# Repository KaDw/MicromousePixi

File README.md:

# Micromouse Pixi #
	
|  |  |
| ----- | ----- |
| Width   | 74mm  |
| Length  | 88mm  |
| Weight  |   |
| Wheels  | 3D printed wheels + MZT-302-30 tyres  |
| Microcontroller  | STM32F405RGT6  |
| Motor/Encoder  | Pololu 10:1 HPCB 3000 obr/min + AS5304 encoders  |
| Battery  | Li-Pol Dualsky 7.4V 150mAh 20C  |
| Motor Driver  | TB6612  |
| Sensor | TEFT4300 + SFH4545 X 6  |
| Gyro | FXAS21002C  |

PCB

### Development tools ###

* STM32CubeMX Version 4.17.0
* HAL Libraries - FW_F4 V1.13.1
* Keil uVision 5.21a
* EagleCAD 7.2
* Autodesk Inventor 2016

Development tools can downloaded [here](https://drive.google.com/open?id=0B6SlddUSFtelRTBFR0EwWk1qT1k)

### Setup ###

* CubeMX setup
You can get HAL libraries by going to Help->Install New Libraries->Firmware PAckage for Family STM32F4.
...

### Who do I talk to? ###

* Karol Trzciński 
* Karol Dworakowski karol1dw@gmail.com

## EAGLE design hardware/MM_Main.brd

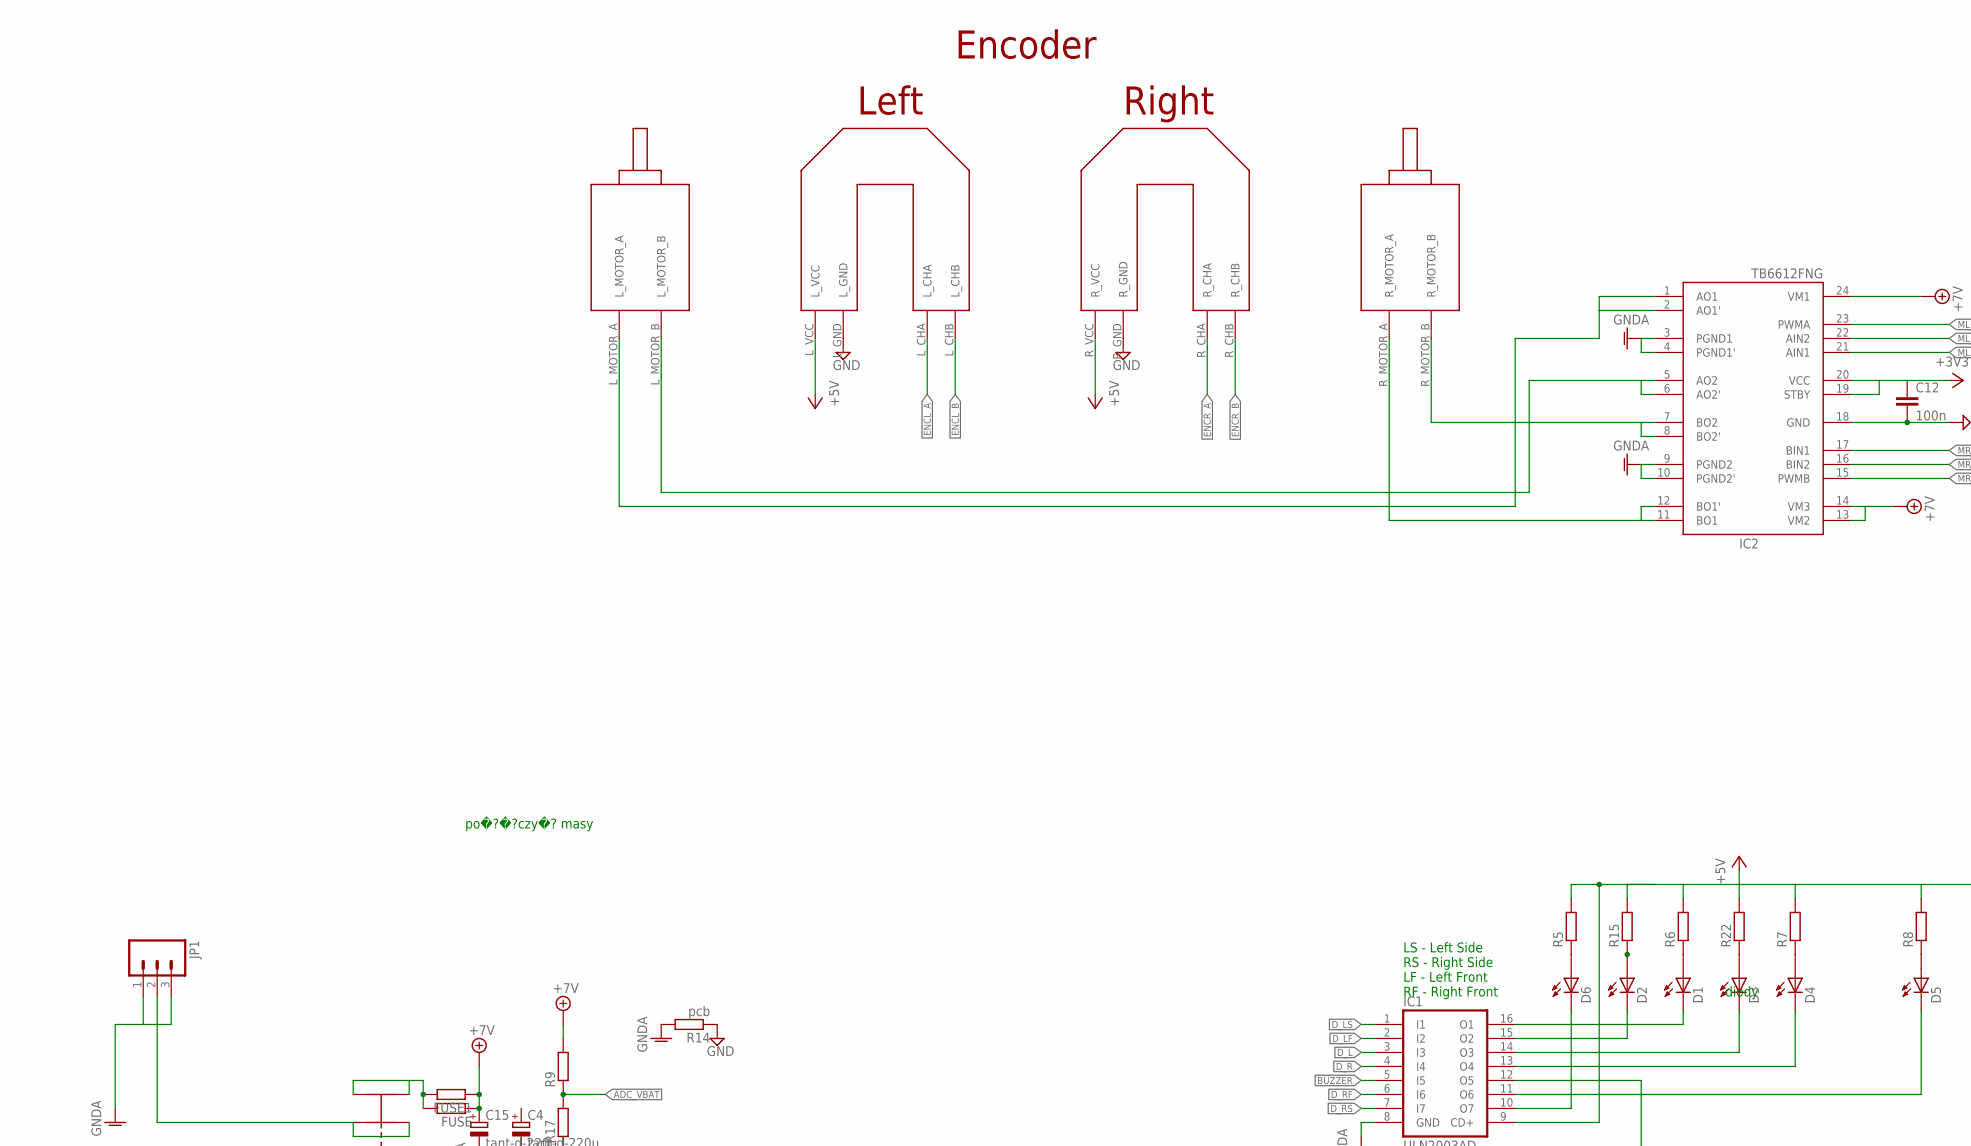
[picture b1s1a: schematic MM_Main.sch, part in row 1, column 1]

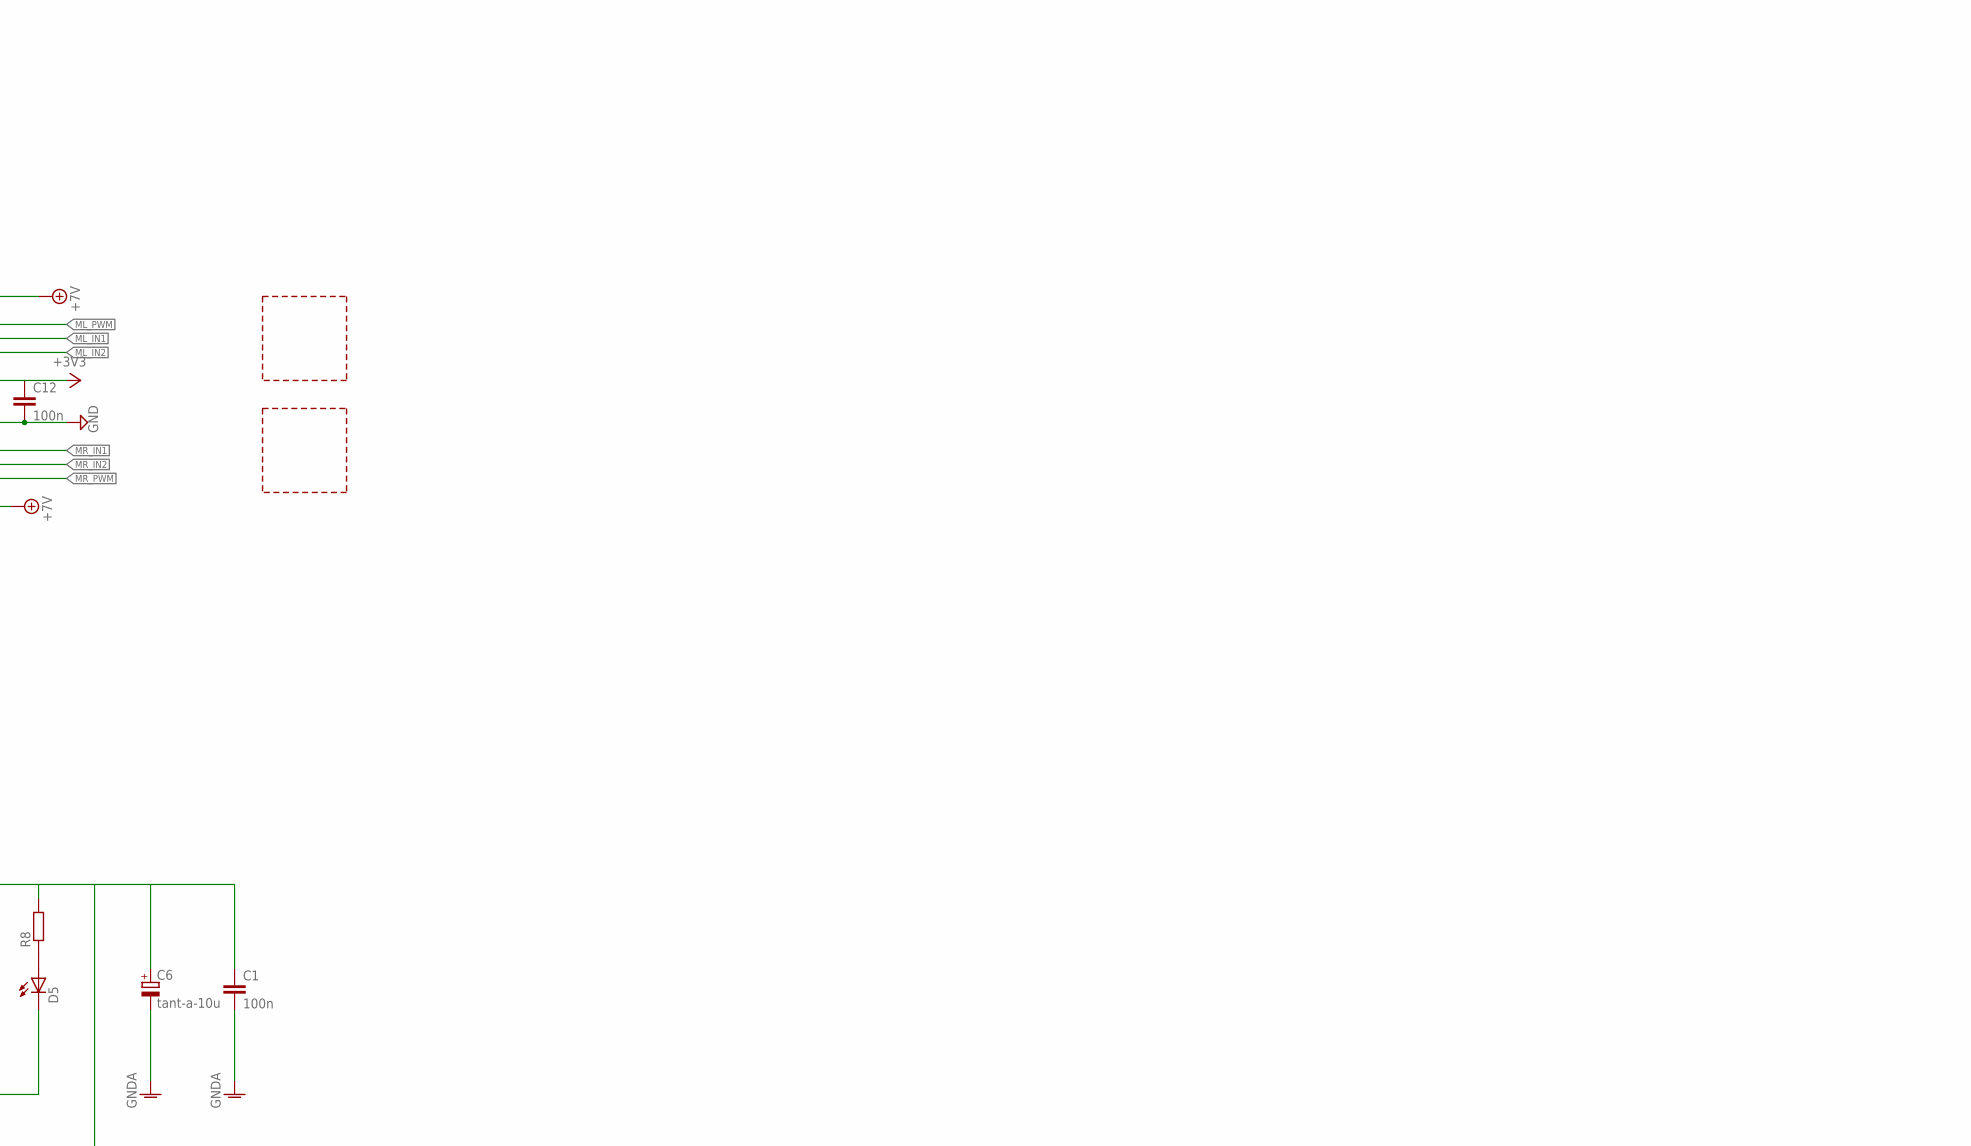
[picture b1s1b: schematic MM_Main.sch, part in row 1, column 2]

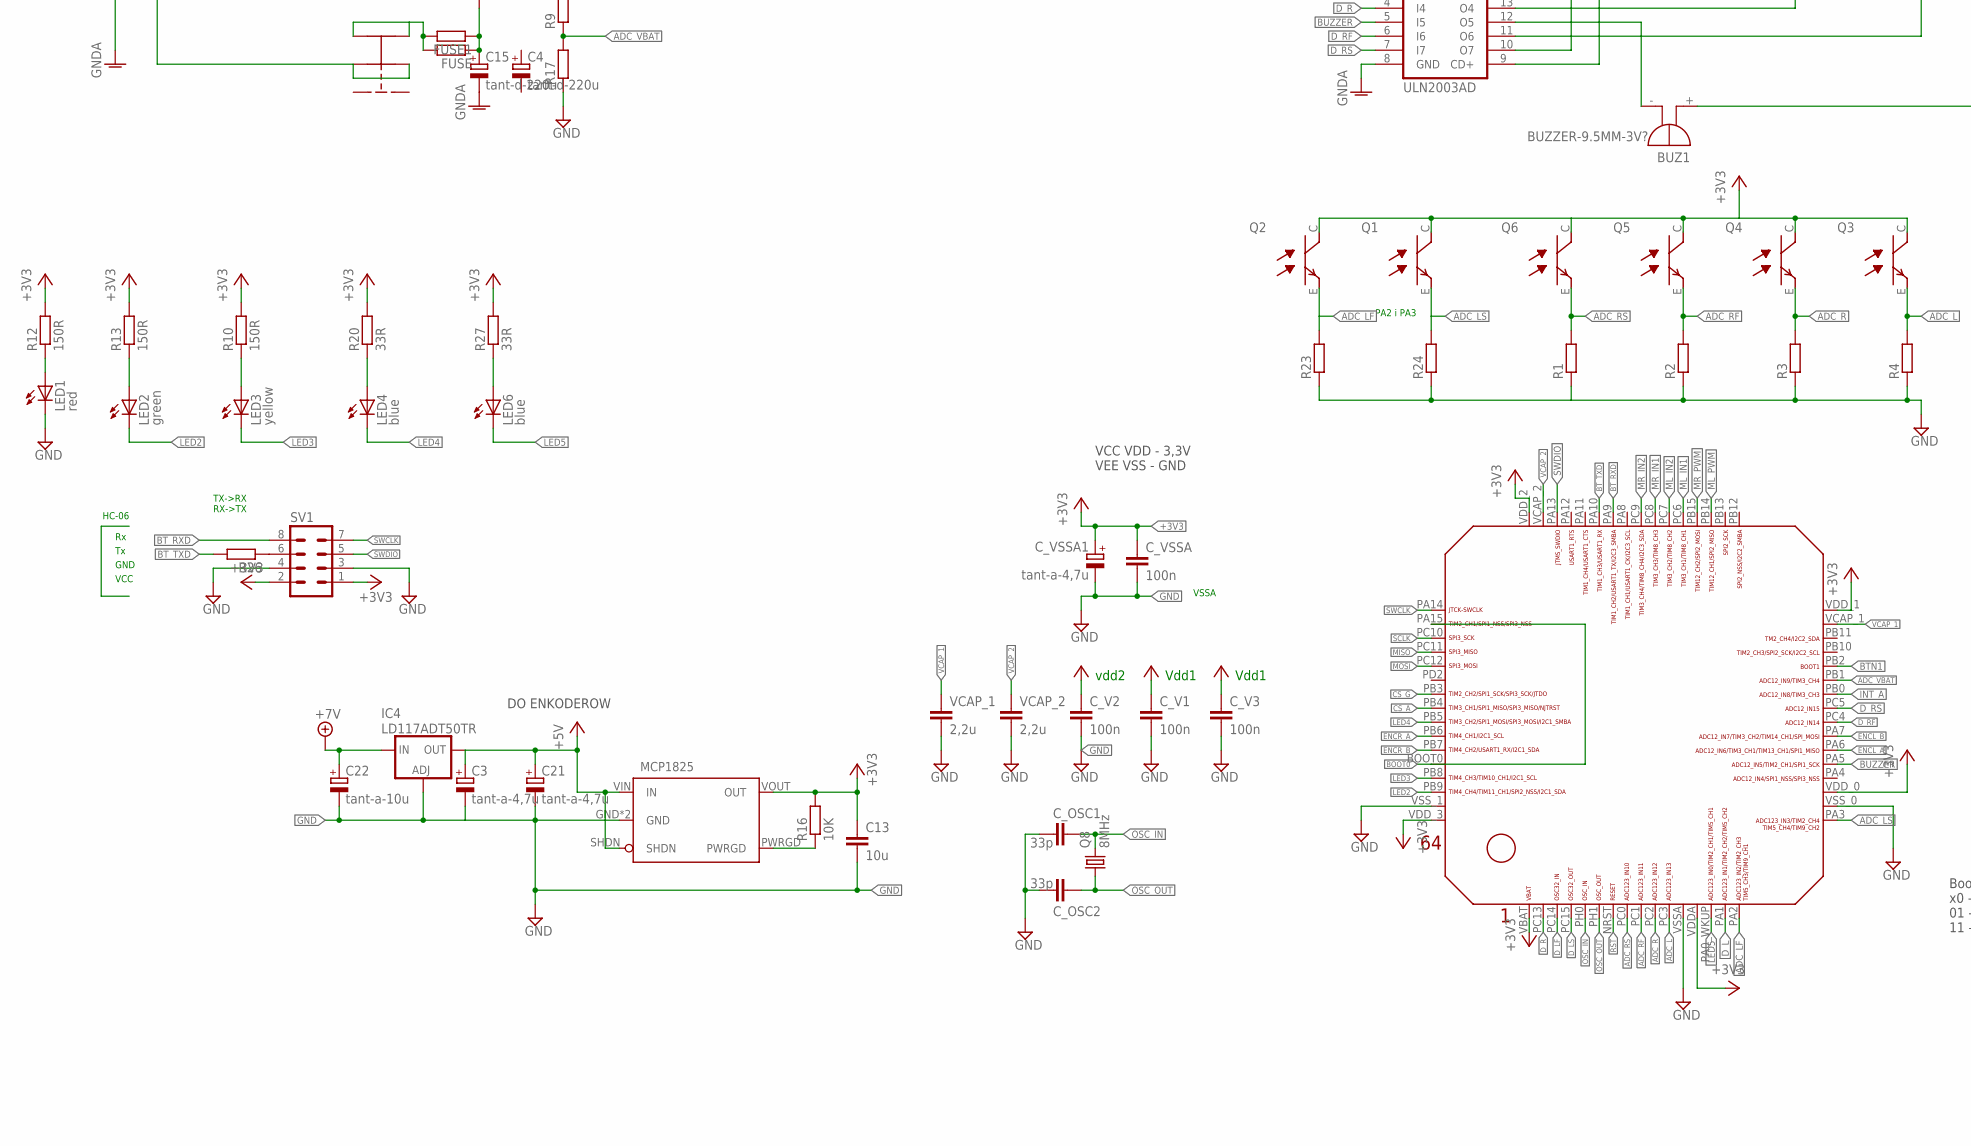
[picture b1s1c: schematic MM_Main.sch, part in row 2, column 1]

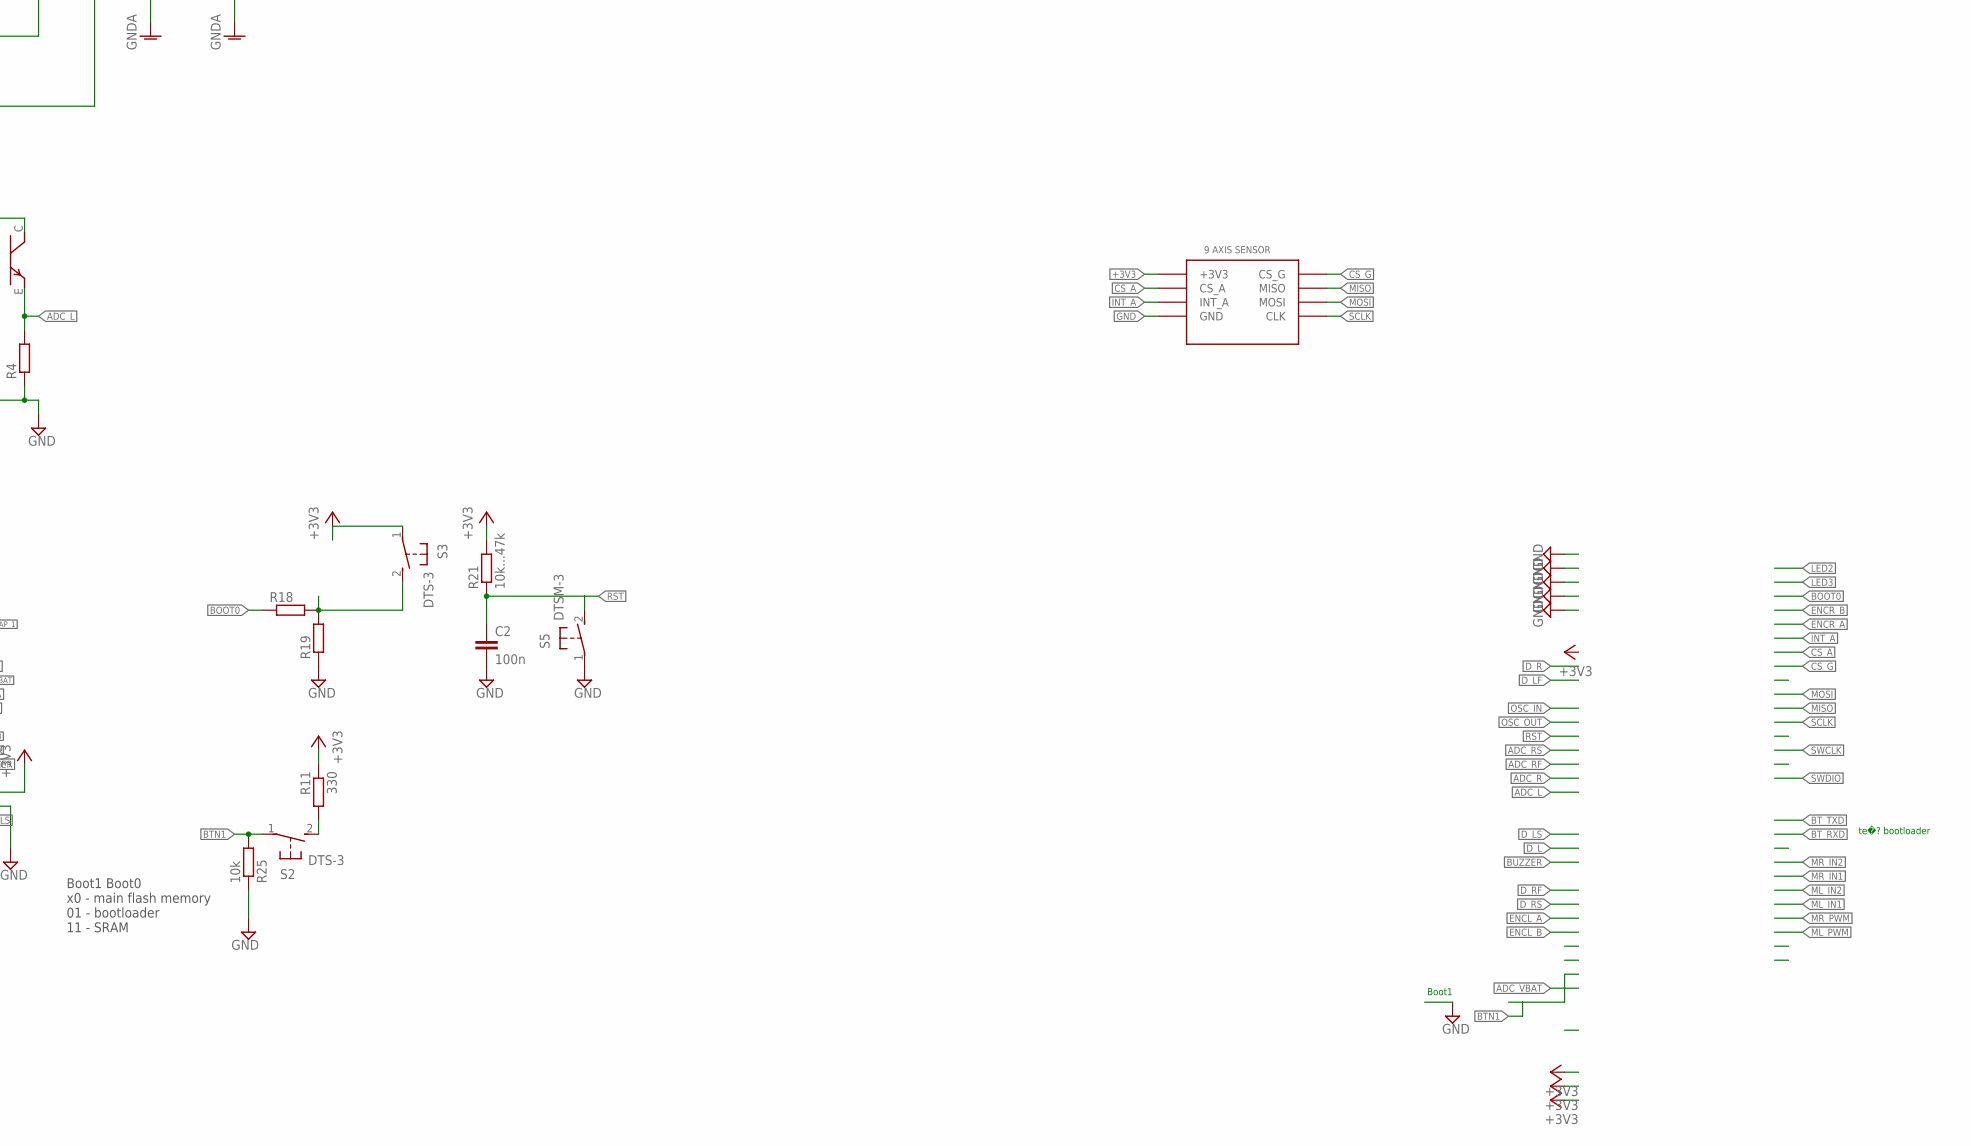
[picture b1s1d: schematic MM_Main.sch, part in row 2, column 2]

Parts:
BUZ1: BUZZER-9.5MM-3V?; BUZZER-9.5MM
C1, C2: 100n; C0805
C3, C21: tant-a-4,7u; SMC_A
C4, C15: tant-d-220u; SMC_D
C6, C22: tant-a-10u; SMC_A
C12: 100n; C0603
C13: 10u; C0805
C_OSC1, C_OSC2: 33p; C0805
C_V1, C_V2, C_V3: 100n; C0805
C_VSSA: 100n; C0805
C_VSSA1: tant-a-4,7u; SMC_A
D1, D2, D3, D4, D5, D6: SFH4545-C
FUSE, FUSE1: R-EU_M3516; M3516
IC1: ULN2003AD; SO16
IC2: TB6612FNG; SSOP24
IC4: LD117ADT50TR; DPACK
IC5: MCP1825; SOT223-5
JP1: M03POLAR; MOLEX-1X3
L1, L2: LABITYNT; LABIRYNT
LED1: red; SML1206
LED2: green; SML1206
LED3: yellow; SML1206
LED4, LED6: blue; SML1206
Q1, Q2, Q3, Q4, Q5, Q6: TEFT4300
Q8: 8MHz; CRYSTAL_5X3.2MM
R1, R2, R3, R4, R5, R6, R7, R8, R9, R15, R17, R18, R19, R22, R23, R24, R26: R-EU_R0805; R0805
R10, R12, R13: 150R; R0805
R11: 330; R0805
R14: pcb; R0201
R16: 10K; R0805
R20, R27: 33R; R0805
R21: 10k...47k; R0805
R25: 10k; R0805
S2, S3: DTS-3
S5: DTSM-3
SV1: MA04-2
U$1: 9AXIS_MODULE; 9AXIS_SENSOR_MODULE
U$3: PRZELACZNIK_SUWAKOWY
U$5: MOTOR_MOUNT
U$6: STM32F4X5; STM32F4-LQFP64
VCAP_1, VCAP_2: 2,2u; C0805

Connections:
+3V3: C12.1, C13.1, C_V1.1, C_V2.1, C_V3.1, C_VSSA.1, C_VSSA1.+, IC2.19 (STBY), IC2.20 (VCC), IC5.VOUT (OUT), Q1.C, Q2.C, Q3.C, Q4.C, Q5.C, Q6.C, R10.2, R11.1, R12.2, R13.2, R16.2, R20.2, R21.2, R27.2, S3.1, SV1.1, SV1.2, U$1.P$1 (+3V3), U$6.VBAT, U$6.VDDA, U$6.VDD_0, U$6.VDD_1, U$6.VDD_2, U$6.VDD_3
+5V: BUZ1.+, C1.1, C3.+, C6.+, C21.+, IC1.9 (CD+), IC4.4 (OUT), IC5.SHDN, IC5.VIN (IN), R5.2, R6.2, R7.2, R8.2, R15.2, R22.2, U$5.L_VCC, U$5.R_VCC
+7V: C15.+, C22.+, FUSE.1, FUSE1.1, IC2.13 (VM2), IC2.14 (VM3), IC2.24 (VM1), IC4.3 (IN), R9.2
ADC_L: Q3.E, R4.2, U$6.PC3
ADC_LF: Q2.E, R23.2, U$6.PA2
ADC_LS: Q1.E, R24.2, U$6.PA3
ADC_R: Q4.E, R3.2, U$6.PC2
ADC_RF: Q5.E, R2.2, U$6.PC1
ADC_RS: Q6.E, R1.2, U$6.PC0
ADC_VBAT: R9.1, R17.2, U$6.PB1
BOOT0: R18.1, U$6.BOOT0, U$6.PA15
BTN1: R25.2, S2.1, U$6.PB2
BT_RXD: SV1.8, U$6.PA9
BT_TXD: R26.2, U$6.PA10
BUZZER: IC1.5 (I5), U$6.PA5
CS_A: U$1.P$2 (CS_A), U$6.PB4
CS_G: U$1.P$8 (CS_G), U$6.PB3
D_L: IC1.3 (I3), U$6.PA1
D_LF: IC1.2 (I2), U$6.PC14
D_LS: IC1.1 (I1), U$6.PC15
D_R: IC1.4 (I4), U$6.PC13
D_RF: IC1.6 (I6), U$6.PC4
D_RS: IC1.7 (I7), U$6.PC5
ENCL_A: U$5.L_CHA, U$6.PA6
ENCL_B: U$5.L_CHB, U$6.PA7
ENCR_A: U$5.R_CHA, U$6.PB6
ENCR_B: U$5.R_CHB, U$6.PB7
GND: C2.2, C3.-, C12.2, C13.2, C21.-, C22.-, C_OSC1.1, C_OSC2.1, C_V1.2, C_V2.2, C_V3.2, C_VSSA.2, C_VSSA1.-, IC2.18 (GND), IC4.1 (ADJ), IC5.GND, IC5.GND_TAB (GND), LED1.C, R1.1, R2.1, R3.1, R4.1, R14.1, R17.1, R19.1, R23.1, R24.1, R25.1, S5.1, SV1.3, SV1.4, U$1.P$4 (GND), U$5.L_GND, U$5.R_GND, U$6.VSSA, U$6.VSS_0, U$6.VSS_1, VCAP_1.2, VCAP_2.2
GNDA: C1.2, C6.-, C15.-, IC1.8 (GND), IC2.3 (PGND1), IC2.4 (PGND1'), IC2.9 (PGND2), IC2.10 (PGND2'), JP1.1, JP1.3, R14.2
INT_A: U$1.P$3 (INT_A), U$6.PB0
LED2: LED2.C, U$6.PB9
LED3: LED3.C, U$6.PB8
LED4: LED4.C, U$6.PB5
LED5: LED6.C, U$6.PA0_WKUP (PA0_AKUP)
MISO: U$1.P$7 (MISO), U$6.PC11
ML_IN1: IC2.22 (AIN2), U$6.PC6
ML_IN2: IC2.21 (AIN1), U$6.PC7
ML_PWM: IC2.23 (PWMA), U$6.PB14
MOSI: U$1.P$6 (MOSI), U$6.PC12
MR_IN1: IC2.17 (BIN1), U$6.PC8
MR_IN2: IC2.16 (BIN2), U$6.PC9
MR_PWM: IC2.15 (PWMB), U$6.PB15
unnamed: IC5.PWRGD, R16.1
unnamed: D2.ANODA (A), R15.1
unnamed: D6.ANODA (A), R5.1
unnamed: IC2.7 (BO2), IC2.8 (BO2'), U$5.R_MOTOR_B
unnamed: IC2.11 (BO1), IC2.12 (BO1'), U$5.R_MOTOR_A
unnamed: IC2.1 (AO1), IC2.2 (AO1'), U$5.L_MOTOR_A
unnamed: LED3.A, R10.1
unnamed: D1.ANODA (A), R6.1
unnamed: D4.ANODA (A), R7.1
unnamed: D5.ANODA (A), R8.1
unnamed: LED1.A, R12.1
unnamed: IC2.5 (AO2), IC2.6 (AO2'), U$5.L_MOTOR_B
unnamed: BUZ1.-, IC1.12 (O5)
unnamed: D3.ANODA (A), R22.1
unnamed: LED2.A, R13.1
unnamed: LED4.A, R20.1
unnamed: R18.2, R19.2, S3.2
unnamed: FUSE.2, FUSE1.2, U$3.3, U$3.6
unnamed: R26.1, SV1.6
unnamed: R11.2, S2.2
unnamed: LED6.A, R27.1
unnamed: JP1.2, U$3.2, U$3.5
OSC_IN: C_OSC1.2, Q8.P$2 (2), U$6.PH0
OSC_OUT: C_OSC2.2, Q8.P$1 (1), U$6.PH1
RST: C2.1, R21.1, S5.2, U$6.NRST
SCLK: U$1.P$5 (CLK), U$6.PC10
SENSOR_L: D3.KATODA (C), IC1.14 (O3)
SENSOR_LF: D2.KATODA (C), IC1.15 (O2)
SENSOR_LS: D1.KATODA (C), IC1.16 (O1)
SENSOR_R: D4.KATODA (C), IC1.13 (O4)
SENSOR_RF: D5.KATODA (C), IC1.11 (O6)
SENSOR_RS: D6.KATODA (C), IC1.10 (O7)
SWCLK: SV1.7, U$6.PA14
SWDIO: SV1.5, U$6.PA13
VCAP_1: U$6.VCAP_1, VCAP_1.1
VCAP_2: U$6.VCAP_2, VCAP_2.1

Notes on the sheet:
diody
Boot1 Boot0 x0 - main flash memory 01 - bootloader 11 - SRAM
DO ENKODEROW
te�? bootloader
Boot1
VSSA
po�?�?czy�? masy
Vdd1
vdd2
VCC VDD - 3,3V VEE VSS - GND
TX->RX RX->TX
PA2 i PA3
GND
VCC
HC-06
LS - Left Side RS - Right Side LF - Left Front RF - Right Front

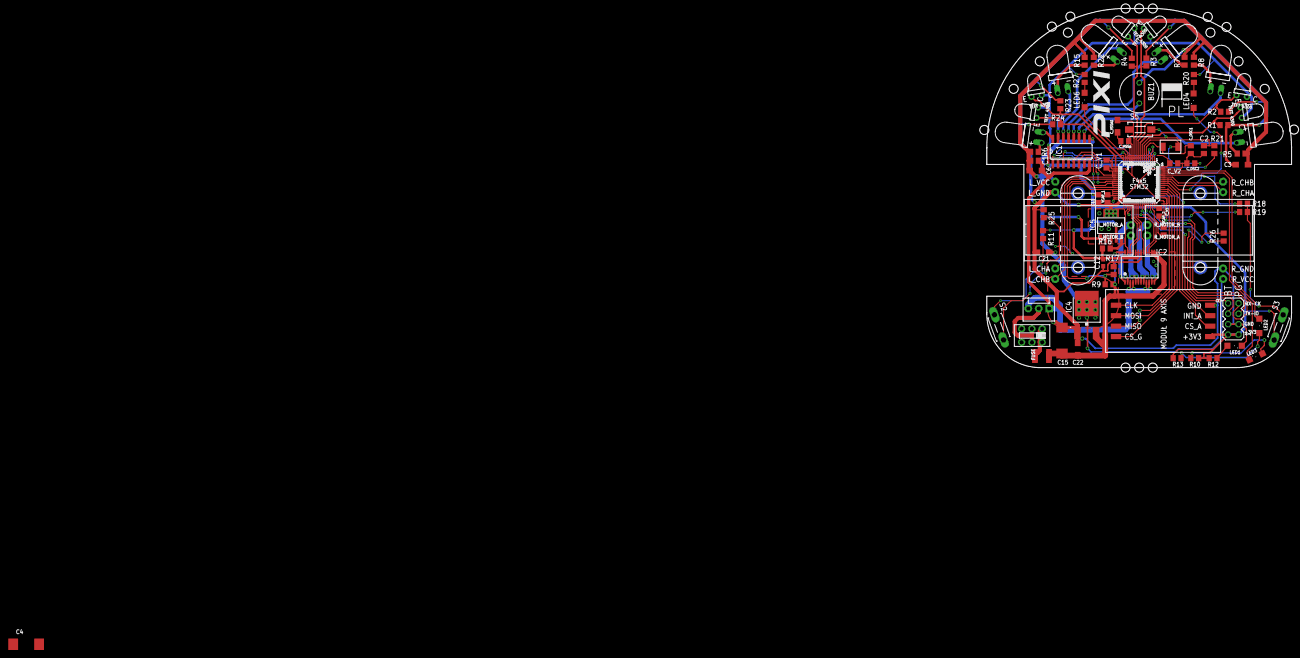
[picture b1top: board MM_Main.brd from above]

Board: 2 copper layers, 74.0 x 87.2 mm, 82 parts (0 on the bottom side), 78 nets.

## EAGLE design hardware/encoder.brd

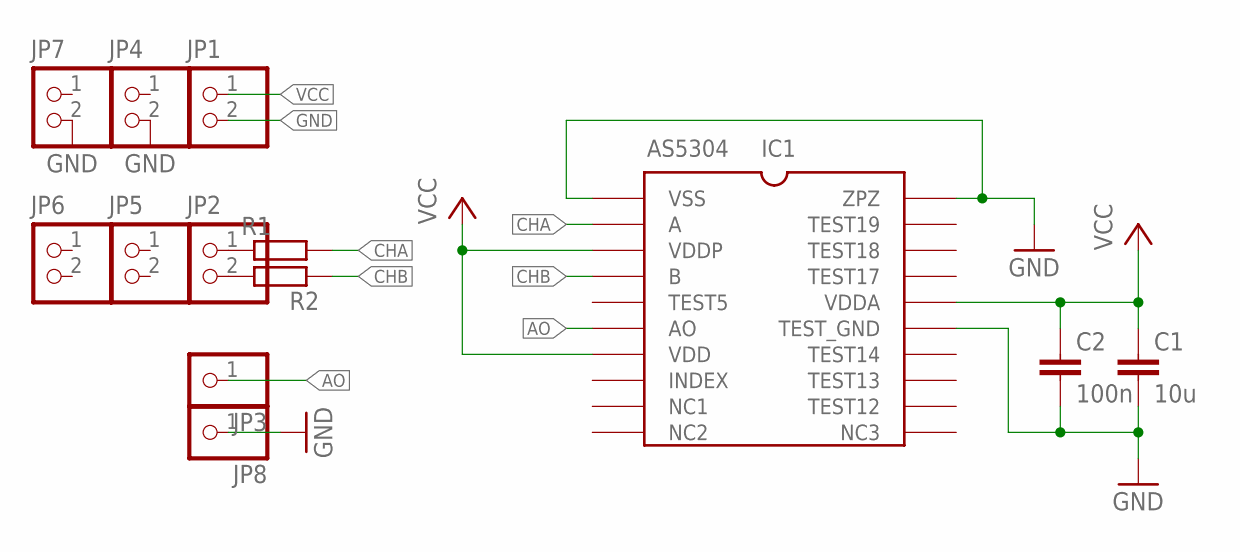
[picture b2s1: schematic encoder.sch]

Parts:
C1: 10u; C0603
C2: 100n; C0603
IC1: AS5304; TSSOP20
JP1, JP2, JP4, JP5, JP6, JP7: PINHD_1X2_ROUND
JP3, JP8: PINHD-1X1; 1X01
R1, R2: R-EU_R0805; R0805

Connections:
AO: IC1.AO, JP3.1
CHA: IC1.A, R1.2
CHB: IC1.B, R2.1
GND: C1.2, C2.2, IC1.TEST_GND, IC1.VSS, IC1.ZPZ, JP1.2, JP4.2, JP7.2, JP8.1
unnamed: JP2.1, R1.1
unnamed: JP2.2, R2.2
VCC: C1.1, C2.1, IC1.VDD, IC1.VDDA, IC1.VDDP, JP1.1

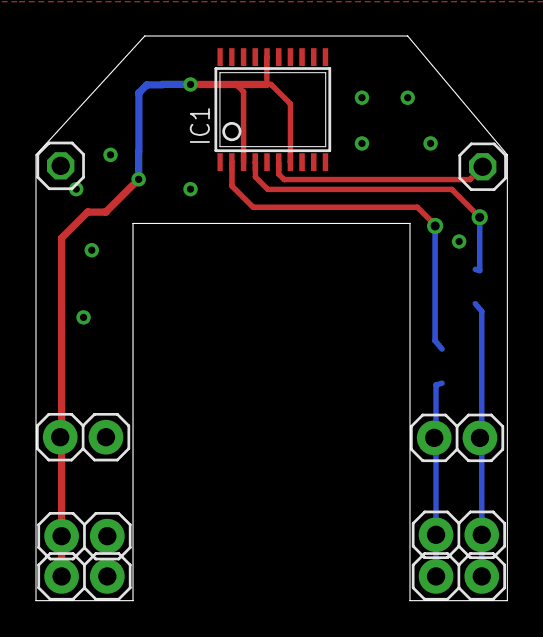
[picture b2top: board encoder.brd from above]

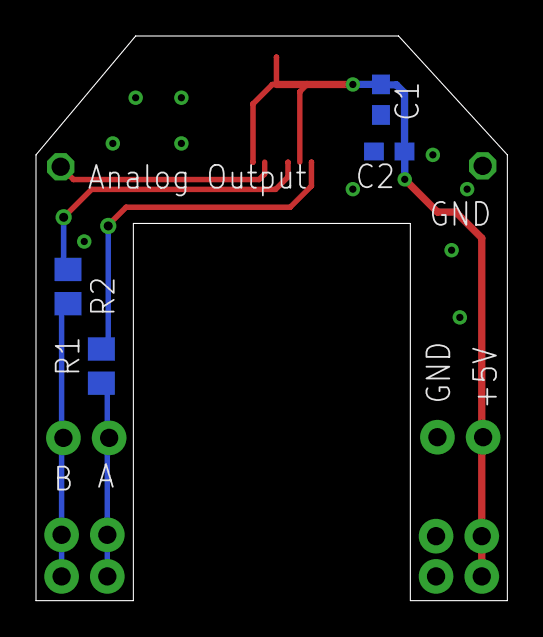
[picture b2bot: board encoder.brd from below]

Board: 2 copper layers, 26.2 x 31.4 mm, 13 parts (4 on the bottom side), 7 nets.

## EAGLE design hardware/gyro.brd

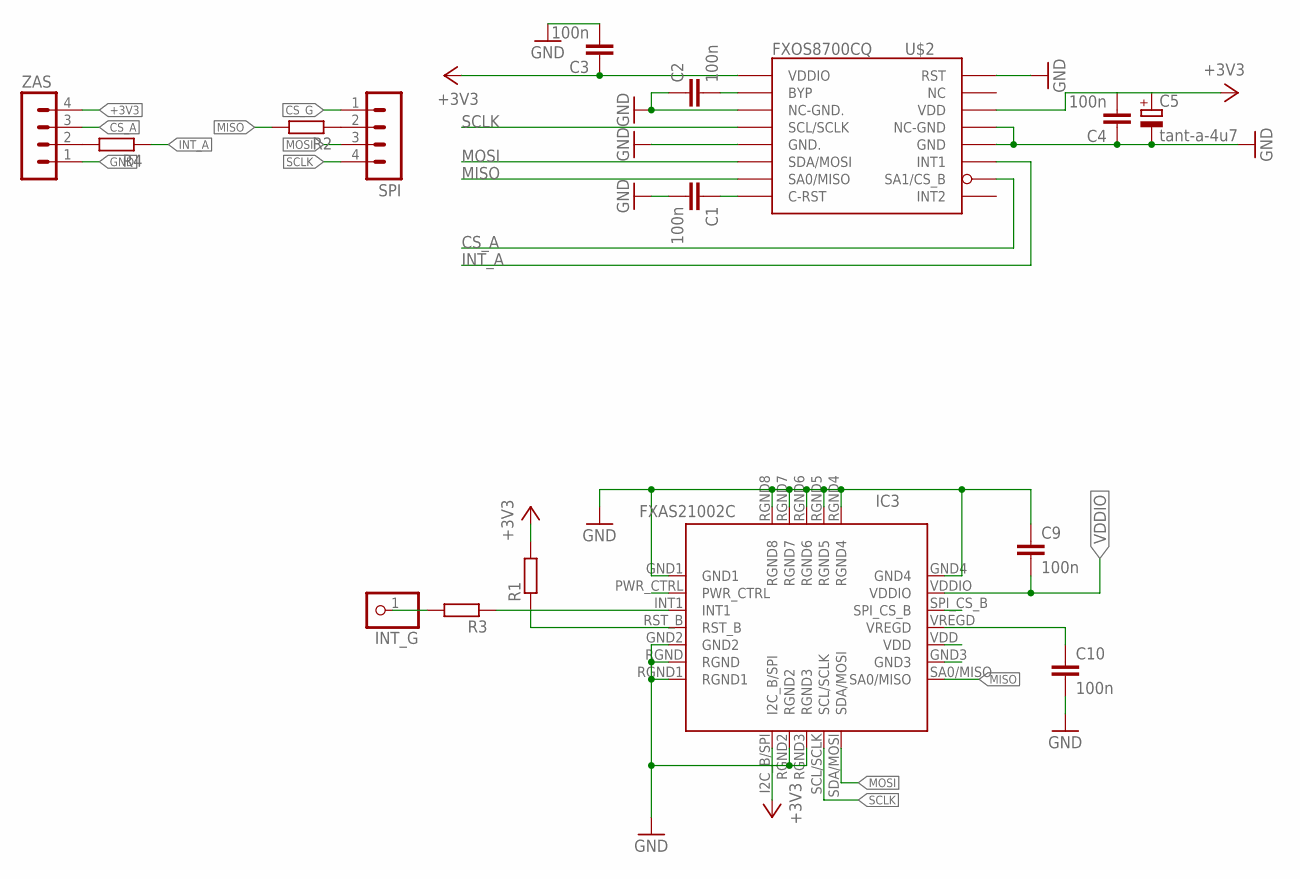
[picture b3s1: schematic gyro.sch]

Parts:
C1, C2, C3, C4, C9, C10: 100n; C0603
C5: tant-a-4u7; SMC_A
IC3: FXAS21002C; QFN24-4X4
INT_G: PINHD-1X1; 1X01
R1, R2, R3, R4: R-EU_R0603; R0603
SPI: MA04-1
U$2: FXOS8700CQR1; QFN16-5X3
ZAS: MA04-1

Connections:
+3V3: C3.1, C4.2, C5.+, IC3.I2C_B/SPI, IC3.VDD, R1.2, U$2.P$1 (VDDIO), U$2.P$14 (VDD), ZAS.4
CS_A: U$2.P$10 (SA1/CS_B), ZAS.3
CS_G: IC3.SPI_CS_B, SPI.1
GND: C1.2, C2.1, C3.2, C4.1, C5.-, C9.1, C10.2, IC3.GND1, IC3.GND2, IC3.GND3, IC3.GND4, IC3.RGND, IC3.RGND1, IC3.RGND2, IC3.RGND3, IC3.RGND4, IC3.RGND5, IC3.RGND6, IC3.RGND7, IC3.RGND8, U$2.P$3 (NC-GND.), U$2.P$5 (GND.), U$2.P$12 (GND), U$2.P$13 (NC-GND), U$2.P$16 (RST), ZAS.1
INT_A: R4.1, U$2.P$11 (INT1)
MISO: IC3.SA0/MISO, R2.2, U$2.P$7 (SA0/MISO)
MOSI: IC3.SDA/MOSI, SPI.3, U$2.P$6 (SDA/MOSI)
unnamed: R2.1, SPI.2
unnamed: INT_G.1, R3.2
unnamed: IC3.INT1, R3.1
unnamed: R4.2, ZAS.2
unnamed: C1.1, U$2.P$8 (C-RST)
unnamed: C2.2, U$2.P$2 (BYP)
unnamed: C10.1, IC3.VREGD
unnamed: IC3.RST_B, R1.1
SCLK: IC3.SCL/SCLK, SPI.4, U$2.P$4 (SCL/SCLK)
VDDIO: C9.2, IC3.VDDIO

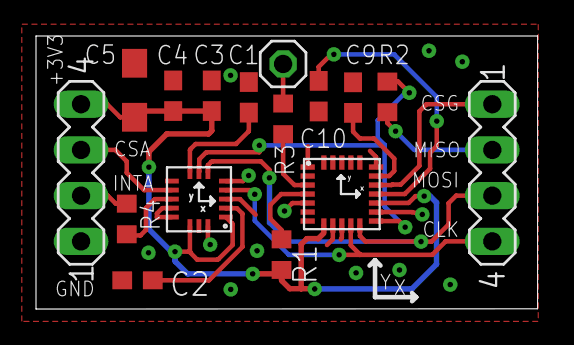
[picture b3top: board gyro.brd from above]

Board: 2 copper layers, 27.9 x 15.2 mm, 16 parts (0 on the bottom side), 17 nets.

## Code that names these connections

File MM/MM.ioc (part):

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Mcu.Name=STM32F405RGTx
Mcu.Package=LQFP64
Mcu.UserName=STM32F405RGTx
PA0-WKUP.GPIOParameters=GPIO_Label
PA0-WKUP.GPIO_Label=LED5
PA0-WKUP.Signal=GPIO_Output
PA1.GPIOParameters=GPIO_Label
PA1.GPIO_Label=D_L
PA1.Signal=GPIO_Output
PA10.GPIOParameters=GPIO_Label
PA10.GPIO_Label=BT_TX
PA10.Mode=Asynchronous
PA10.Signal=USART1_RX
PA13.Mode=Serial-Wire
PA13.Signal=SYS_JTMS-SWDIO
PA14.Mode=Serial-Wire
PA14.Signal=SYS_JTCK-SWCLK
PA15.GPIOParameters=GPIO_Label
PA15.GPIO_Label=BTN0
PA15.Signal=GPXTI15
PA2.GPIOParameters=GPIO_Label
PA2.GPIO_Label=ADC_LF
PA2.Signal=ADCx_IN2
PA3.GPIOParameters=GPIO_Label
PA3.GPIO_Label=ADC_LS
PA3.Signal=ADCx_IN3
PA5.GPIOParameters=GPIO_Label
PA5.GPIO_Label=BUZZER
PA5.Signal=GPIO_Output
PA6.GPIOParameters=GPIO_Label
PA6.GPIO_Label=ENCL_A
PA6.Signal=S_TIM3_CH1
PA7.GPIOParameters=GPIO_Label
PA7.GPIO_Label=ENCL_B
PA7.Signal=S_TIM3_CH2
PA9.GPIOParameters=GPIO_Label
PA9.GPIO_Label=BT_TX
PA9.Mode=Asynchronous
PA9.Signal=USART1_TX
PB0.GPIOParameters=GPIO_Label
PB0.GPIO_Label=INT_A
PB0.Signal=GPIO_Input
PB1.GPIOParameters=GPIO_Label
PB1.GPIO_Label=ADC1_VBAT
PB1.Signal=ADCx_IN9
PB14.GPIOParameters=GPIO_Label
PB14.GPIO_Label=ML_PWM
PB14.Signal=S_TIM12_CH1
PB15.GPIOParameters=GPIO_Label
PB15.GPIO_Label=MR_PWM
PB15.Signal=S_TIM12_CH2
PB2.GPIOParameters=GPIO_Label
PB2.GPIO_Label=BTN1
PB2.Signal=GPXTI2
PB3.GPIOParameters=GPIO_Label
PB3.GPIO_Label=CS_G
PB3.Signal=GPIO_Output
PB4.GPIOParameters=GPIO_Label
PB4.GPIO_Label=CS_A
PB4.Signal=GPIO_Output
PB5.GPIOParameters=GPIO_Label
PB5.GPIO_Label=LED3
PB5.Signal=GPIO_Output
PB6.GPIOParameters=GPIO_Label
PB6.GPIO_Label=ENCR_A
PB6.Signal=S_TIM4_CH1
PB7.GPIOParameters=GPIO_Label
PB7.GPIO_Label=ENCR_B
PB7.Signal=S_TIM4_CH2
PB8.GPIOParameters=GPIO_Label
PB8.GPIO_Label=LED2
PB8.Signal=GPIO_Output
PB9.GPIOParameters=GPIO_Label
PB9.GPIO_Label=LED1
PB9.Signal=GPIO_Output
PC0.GPIOParameters=GPIO_Label
PC0.GPIO_Label=ADC_RS
PC0.Signal=ADCx_IN10
PC1.GPIOParameters=GPIO_Label
PC1.GPIO_Label=ADC_RF
PC1.Signal=ADCx_IN11
PC10.Mode=Full_Duplex_Master
PC10.Signal=SPI3_SCK
PC11.Mode=Full_Duplex_Master
PC11.Signal=SPI3_MISO
PC12.Mode=Full_Duplex_Master
PC12.Signal=SPI3_MOSI
PC13-ANTI_TAMP.GPIOParameters=GPIO_Label
PC13-ANTI_TAMP.GPIO_Label=D_R
PC13-ANTI_TAMP.Signal=GPIO_Output
PC14-OSC32_IN.GPIOParameters=GPIO_Label
PC14-OSC32_IN.GPIO_Label=D_LF
PC14-OSC32_IN.Signal=GPIO_Output
PC15-OSC32_OUT.GPIOParameters=GPIO_Label
PC15-OSC32_OUT.GPIO_Label=D_LS
PC15-OSC32_OUT.Signal=GPIO_Output
PC2.GPIOParameters=GPIO_Label
PC2.GPIO_Label=ADC_R
PC2.Signal=ADCx_IN12
PC3.GPIOParameters=GPIO_Label
PC3.GPIO_Label=ADC_L
PC3.Signal=ADCx_IN13
PC4.GPIOParameters=GPIO_Label
PC4.GPIO_Label=D_RF
PC4.Signal=GPIO_Output
PC5.GPIOParameters=GPIO_Label
PC5.GPIO_Label=D_RS
PC5.Signal=GPIO_Output
PC6.GPIOParameters=GPIO_Label
PC6.GPIO_Label=ML_IN1
PC6.Signal=GPIO_Analog
PC7.GPIOParameters=GPIO_Label
PC7.GPIO_Label=ML_IN2
PC7.Signal=GPIO_Analog
PC8.GPIOParameters=GPIO_Label
PC8.GPIO_Label=MR_IN1
PC8.Signal=GPIO_Output
PC9.GPIOParameters=GPIO_Label
PC9.GPIO_Label=MR_IN2
PC9.Signal=GPIO_Output
PH0-OSC_IN.Mode=HSE-External-Oscillator
PH0-OSC_IN.Signal=RCC_OSC_IN
PH1-OSC_OUT.Mode=HSE-External-Oscillator
PH1-OSC_OUT.Signal=RCC_OSC_OUT
RCC.HSE_VALUE=8000000
RCC.SYSCLKFreq_VALUE=168000000
RCC.SYSCLKSource=RCC_SYSCLKSOURCE_PLLCLK
board=MM

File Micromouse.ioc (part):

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Mcu.Name=STM32F405RGTx
Mcu.Package=LQFP64
Mcu.UserName=STM32F405RGTx
PA0-WKUP.GPIOParameters=GPIO_Label
PA0-WKUP.GPIO_Label=LED4
PA0-WKUP.Signal=GPIO_Output
PA1.GPIOParameters=GPIO_Label
PA1.GPIO_Label=D_L
PA1.Signal=GPIO_Output
PA10.GPIOParameters=GPIO_Label
PA10.GPIO_Label=BT_TX
PA10.Mode=Asynchronous
PA10.Signal=USART1_RX
PA13.Mode=Serial-Wire
PA13.Signal=SYS_JTMS-SWDIO
PA14.Mode=Serial-Wire
PA14.Signal=SYS_JTCK-SWCLK
PA15.GPIOParameters=GPIO_PuPd,GPIO_Label
PA15.GPIO_Label=BTN2
PA15.GPIO_PuPd=GPIO_PULLDOWN
PA15.Signal=GPXTI15
PA2.GPIOParameters=GPIO_Label
PA2.GPIO_Label=ADC_LF
PA2.Signal=ADCx_IN2
PA3.GPIOParameters=GPIO_Label
PA3.GPIO_Label=ADC_LS
PA3.Signal=ADCx_IN3
PA5.GPIOParameters=GPIO_Label
PA5.GPIO_Label=BUZZER
PA5.Signal=GPIO_Output
PA6.GPIOParameters=GPIO_PuPd,GPIO_Label
PA6.GPIO_Label=ENCL_A
PA6.GPIO_PuPd=GPIO_PULLDOWN
PA6.Signal=S_TIM3_CH1
PA7.GPIOParameters=GPIO_PuPd,GPIO_Label
PA7.GPIO_Label=ENCL_B
PA7.GPIO_PuPd=GPIO_PULLDOWN
PA7.Signal=S_TIM3_CH2
PA9.GPIOParameters=GPIO_Label
PA9.GPIO_Label=BT_TX
PA9.Mode=Asynchronous
PA9.Signal=USART1_TX
PB0.GPIOParameters=GPIO_Label,GPIO_ModeDefaultEXTI
PB0.GPIO_Label=INT_G
PB0.GPIO_ModeDefaultEXTI=GPIO_MODE_IT_FALLING
PB0.Signal=GPXTI0
PB1.GPIOParameters=GPIO_Label
PB1.GPIO_Label=ADC_VBAT
PB1.Signal=ADCx_IN9
PB14.GPIOParameters=GPIO_Label
PB14.GPIO_Label=ML_PWM
PB14.Signal=S_TIM12_CH1
PB15.GPIOParameters=GPIO_Label
PB15.GPIO_Label=MR_PWM
PB15.Signal=S_TIM12_CH2
PB2.GPIOParameters=GPIO_PuPd,GPIO_Label,GPIO_ModeDefaultEXTI
PB2.GPIO_Label=BTN
PB2.GPIO_ModeDefaultEXTI=GPIO_MODE_IT_FALLING
PB2.GPIO_PuPd=GPIO_PULLDOWN
PB2.Signal=GPXTI2
PB3.GPIOParameters=GPIO_PuPd,GPIO_Label
PB3.GPIO_Label=CS_G
PB3.GPIO_PuPd=GPIO_PULLUP
PB3.Signal=GPIO_Output
PB4.GPIOParameters=GPIO_Label
PB4.GPIO_Label=CS_A
PB4.Signal=GPIO_Output
PB5.GPIOParameters=GPIO_Label
PB5.GPIO_Label=LED3
PB5.Signal=GPIO_Output
PB6.GPIOParameters=GPIO_PuPd,GPIO_Label
PB6.GPIO_Label=ENCR_A
PB6.GPIO_PuPd=GPIO_PULLDOWN
PB6.Signal=S_TIM4_CH1
PB7.GPIOParameters=GPIO_PuPd,GPIO_Label
PB7.GPIO_Label=ENCR_B
PB7.GPIO_PuPd=GPIO_PULLDOWN
PB7.Signal=S_TIM4_CH2
PB8.GPIOParameters=GPIO_Label
PB8.GPIO_Label=LED2
PB8.Signal=GPIO_Output
PB9.GPIOParameters=GPIO_Label
PB9.GPIO_Label=LED1
PB9.Signal=GPIO_Output
PC0.GPIOParameters=GPIO_Label
PC0.GPIO_Label=ADC_RS
PC0.Signal=ADCx_IN10
PC1.GPIOParameters=GPIO_Label
PC1.GPIO_Label=ADC_RF
PC1.Signal=ADCx_IN11
PC10.Mode=Full_Duplex_Master
PC10.Signal=SPI3_SCK
PC11.Mode=Full_Duplex_Master
PC11.Signal=SPI3_MISO
PC12.Mode=Full_Duplex_Master
PC12.Signal=SPI3_MOSI
PC13-ANTI_TAMP.GPIOParameters=GPIO_Label
PC13-ANTI_TAMP.GPIO_Label=D_R
PC13-ANTI_TAMP.Signal=GPIO_Output
PC14-OSC32_IN.GPIOParameters=GPIO_Label
PC14-OSC32_IN.GPIO_Label=D_LF
PC14-OSC32_IN.Signal=GPIO_Output
PC15-OSC32_OUT.GPIOParameters=GPIO_Label
PC15-OSC32_OUT.GPIO_Label=D_LS
PC15-OSC32_OUT.Signal=GPIO_Output
PC2.GPIOParameters=GPIO_Label
PC2.GPIO_Label=ADC_R
PC2.Signal=ADCx_IN12
PC3.GPIOParameters=GPIO_Label
PC3.GPIO_Label=ADC_L
PC3.Signal=ADCx_IN13
PC4.GPIOParameters=GPIO_Label
PC4.GPIO_Label=D_RF
PC4.Signal=GPIO_Output
PC5.GPIOParameters=GPIO_Label
PC5.GPIO_Label=D_RS
PC5.Signal=GPIO_Output
PC6.GPIOParameters=GPIO_Label
PC6.GPIO_Label=ML_IN1
PC6.Signal=GPIO_Output
PC7.GPIOParameters=GPIO_Label
PC7.GPIO_Label=ML_IN2
PC7.Signal=GPIO_Output
PC8.GPIOParameters=GPIO_Label
PC8.GPIO_Label=MR_IN1
PC8.Signal=GPIO_Output
PC9.GPIOParameters=GPIO_Label
PC9.GPIO_Label=MR_IN2
PC9.Signal=GPIO_Output
PH0-OSC_IN.Mode=HSE-External-Oscillator
PH0-OSC_IN.Signal=RCC_OSC_IN
PH1-OSC_OUT.Mode=HSE-External-Oscillator
PH1-OSC_OUT.Signal=RCC_OSC_OUT
RCC.HSE_VALUE=8000000
RCC.SYSCLKFreq_VALUE=168000000
RCC.SYSCLKSource=RCC_SYSCLKSOURCE_PLLCLK
board=Micromouse

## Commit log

2015-11-26 test
2015-11-28 dodalem schemat z jednym golpinem i biblioteke z enkoderem
2015-12-01 bibloteki, szkic i plytka glowna
2015-12-03 bilbiotek od mm, zeby nie dodawac za kazdym razem Eagle->use
2015-12-04 biblioteka do gyro
2015-12-04 blioteka do gyro
2015-12-04 biblioteka do gryo
2015-12-05 dodanie tStop przy padach i w srodku gyro i acc
2015-12-05 dodanie tranzystorow do diod
2015-12-12 pcb gyro stm
2015-12-12 poprawka do diod i stabilizatora
2015-12-18 Eagle.gitignore created online with Bitbucket
2015-12-18 gitignore i sch
2015-12-18 main.brd deleted online with Bitbucket
2015-12-18 main.sch deleted online with Bitbucket
2015-12-31 Dodanie CubeMX
2016-01-01 dodanie stm32f4 do lib
2016-01-03 gyro na master
2016-01-03 restrict do lbr acc
2016-01-03 INT_A i dopasowanie goldpinow
2016-01-04 polaczenie bibliotek, brakuje jeszcze enkoderow`
2016-01-04 enkodery w bibliotece
2016-01-04 pcb do enkoderow i poprawione lbr
2016-01-05 dodanie wymiarowania do gyro i zepsucie termali :P
2016-01-05 drobna aktualizacja
2016-01-05 gora jest juz prawie gotowa, trzeba jeszcze rozmiescic kondensatory
2016-01-05 poprawilem poligon w gryo
2016-01-05 dodany buzzer w lbr i sch
2016-01-06 wszystkie sciezki polaczone \!
2016-01-06 czesciowy DRC
2016-01-09 renament - 4 LED + all on top
2016-01-09 rozwoj brd
2016-01-09 aktualizacja brd
2016-01-10 brd prawie gotowe
2016-01-10 wszystko polaczone, trzeba dopiscic
2016-01-12 poprawilem zasilanie, rx/tx, obudowa stmki
2016-01-12 dodalem stm32f4 do biblioteki
2016-01-14 nowe gniazdo do zas
2016-01-15 dodalem adxrs620
2016-01-15 gyro gotowe! w lbr pozmieniane poligony
2016-01-16 zmiana gniazda zasilania, VCC i VSS
2016-01-16 no male dodatki
2016-01-18 rozwoj pcb
2016-01-18 poczatek 6LED -- dlugi przod
2016-01-20 zmieniony przod i kolejnosc ledow
2016-01-20 drobna zmiana przy laczeniu masy i leda
2016-01-20 gerbery do gyro
2016-01-21 6 diod
2016-01-21 6LED pcd prawie pusty przod
2016-01-21 wszystko polaczone, zmiana w gyro z vcc na +3v3
2016-01-23 taki rozstaw diod?
2016-01-23 2 zwykle ledy z przodu
2016-01-23 dopasowanie dimension, dodanie otworow i radiatorow, DRC
2016-01-24 drc, kosmetyka, opisy, pasztet
2016-01-25 poprawa bledow, dodanie rezystorow na wyjsciach stm-glownie w modolach, poprawa elementu 9axis z biblioteki
2016-01-26 pixi
2016-01-26 poprawka do silnikow
2016-01-26 dodany napis
2016-01-28 drobna zmiana switch'y
2016-01-28 w poprzednim jest maly blad
2016-01-29 poprawilem przelotki i ustawilem napisy
2016-01-29 poprawki warst opisowych, dodanie gerberow mm
2016-01-31 male zmiany
2016-01-31 jeszcze mniejsze zmiany
2016-01-31 gerbery
2016-01-31 nazwy diod teraz do siebie pasuja
2016-02-02 zamiana warstw
2016-02-09 schamat kodu z CubeMX
2016-02-10 lista elementow w txt
2016-02-12 poprawione przyciski, kwarc i wylacznik zasilania
2016-02-12 PD2 zamienione z PA15
2016-02-12 dodany suwak i miejsce na 2 lipo
2016-02-13 gerbery, tym razem generowane z .cam od satlandu
2016-02-13 to 2 gniazdo moze szorowac o kolo... zmienilem tez konfiguuracje power-switcha, bo tak patrzac na strone electro-parku to tak odczyruje ta konfiguracje, zrobilem drc
2016-02-14 drobne poprawki, chyba koniec :P
2016-02-18 wywalilem elementy ktore byly pod podstawka silnika
2016-02-24 poprawione piny w cubemx
2016-02-24 cubemx+ nowe gerbery
2016-02-27 gerbery z flaga i bez flagi, dodalem te dziurki na koncu
2016-02-28 wieksze otwory dla buzzera
2016-02-28 projekt w Keil + motor.c
2016-03-24 Nowy projekt keil
2016-04-03 UI start
2016-04-13 Beep, BeepInit LedInit...
2016-04-26 porzadki i jeden kod
2016-04-26 poprawa bledow w (glownie motor.c) - enkodery dzialaja nierownomiernie
2016-04-27 tinylib
2016-04-29 juz jest ADC do fototranzystorow
2016-05-03 sprawdzanie baterii, czytanie z gyro
2016-05-04 setPWMRaw dziala, Go nie dziala
2016-05-06 cos tam sie juz kreci
2016-05-06 moje kombinacje
2016-05-06 change .gitignore
2016-05-07 gyro w przerwaniu
2016-05-09 Sterownik PID
2016-05-10 dziala
2016-05-10 apply .gitignore
2016-05-10 Usuniecie folderu z plikami *.o *.d *.crf... Micromouse/MDK_ARM/Micromouse/*
2016-05-11 PID predkosciowy i diody dzialaja
2016-05-12 symulator
2016-05-12 stary symulator, ale dzialajacy
2016-05-12 nowy, nie wpelni dzialajacy sym
2016-05-12 poprawki do sterownika
2016-05-12 poprawka do sterownika
2016-05-15 dalej te PID'y..
2016-05-16 Dzialajacy PID
2016-05-17 gra i buczy
2016-05-17 proboje dodac diody
2016-05-18 usuwanie zbednych plikow
2016-05-22 dodalem DMA do SPI, gyro dziala poprawnie
2016-05-23 pid oparty na czasie
2016-05-24 drobne poprawki
2016-05-28 poprawka do diod
2016-05-29 nic nowego
2016-06-01 zmiana kierunku gyro
2016-06-04 do kazdej funkcji gryo podajemy czas w sekundach
2016-06-06 To sie kreci
2016-06-06 Jestem sklonny do tego, aby wrocic do koncepcji c predkoscia wzspolna i roznicowa
2016-08-24 UART is now using DMA
2016-09-27 gyro in loop
2016-09-28 fxas21002 clean-up
2016-09-30 buzzer wielowatkowy, pozadkowanie kodu w motorze
2016-10-01 motor driver v3
2016-10-02 added MotorStepResponse function
2016-10-02 added _itoa, _ftoa, _strrev
2016-10-06 To dziala - jezdzi do przodu i do tylu, ale jeszcze nie skreca zas dobrze
2016-10-12 modyfikacja
2016-10-12 poprawilem enkodery
2016-10-12 new driver
2016-10-16 cleanup VV.py, poprawilem liczenie predkosci, todo przejechac cala droge
2016-10-17 kolejne debugowanie
2016-10-19 Poprawiono UI_DelauUs i UI_TimeElapsed -> UI_TimeElapsedUs, MotorTurnA jest na if'ach
2016-10-20 motor driver
2016-10-21 dobrane wspolczynniki PID
2016-10-22 poprawione adc do ledow
2016-10-25 naprawa resetu enkoderow, zmiana definicji SENS_XX na sens[x] a nie sensor[x].sens, dodanie wyswietlania nastaw, zmiana wskaznika zwracanego przez _ftoa i itoa na ostatni, a nie pierwszy element
2016-11-14 README.md edited online with Bitbucket
2016-11-15 Regulator translacyjno-rotacyjny na bazie starego
2016-11-18 dodane modele kol i podstawki silnikow
2016-11-24 Linearyzacja LED
2016-11-29 Jazda wzdluz scianki - wersja alfa
2017-01-04 przenioselm MM_sym do repo
2017-03-20 kolejka do silnikow
2017-05-03 test mapowania
2017-10-14 male poprawki do map

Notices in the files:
parts and their libraries:
SparkFun-Connectors: Licensing: Creative Commons ShareAlike 4.0 International - https://creativecommons.org/licenses/by-sa/4.0
